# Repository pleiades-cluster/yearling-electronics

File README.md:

# yearling-electronics
PROVES-Yearling Project files for CD&amp;H and EPS boards

C&DH Board Design Requirements: 
The Command and Data Handling (C&DH) Board is the link between our satellite and the rest of the world. The C&DH board will also handle the broad level scheduling of satellite activities. 

Key Requirements: 

- Facilitate Radio Receive and Transmit 
- Collect Satellite State of Health Data 
- Process Satellite Data into Packets for Transmission 
- Schedule High Level Satellite Activities 

Would be nice: 
- Facilitate a live engineering data link with other processors onboard the satellite 
- EPS Board Design Requirements: 

Non-Optional:
- Overcharge Protection
- Overdischarge Protection
- Solar Charging Circuit 
- 3.3V Regulator
- 5V Regulator 
- Inhibit Scheme 
- Battery Monitor

Very Preferred:
- Direct RP2040 Control On-Board 
- Battery Fuel Gauge 
- Power Path Circuit
- Battery Thermal Management 

Would be Nice:
- Circuit Breaker System 
- Resettable Fuses 

The EPS board will be a hybrid of the PyCubed and OreSat architectures.

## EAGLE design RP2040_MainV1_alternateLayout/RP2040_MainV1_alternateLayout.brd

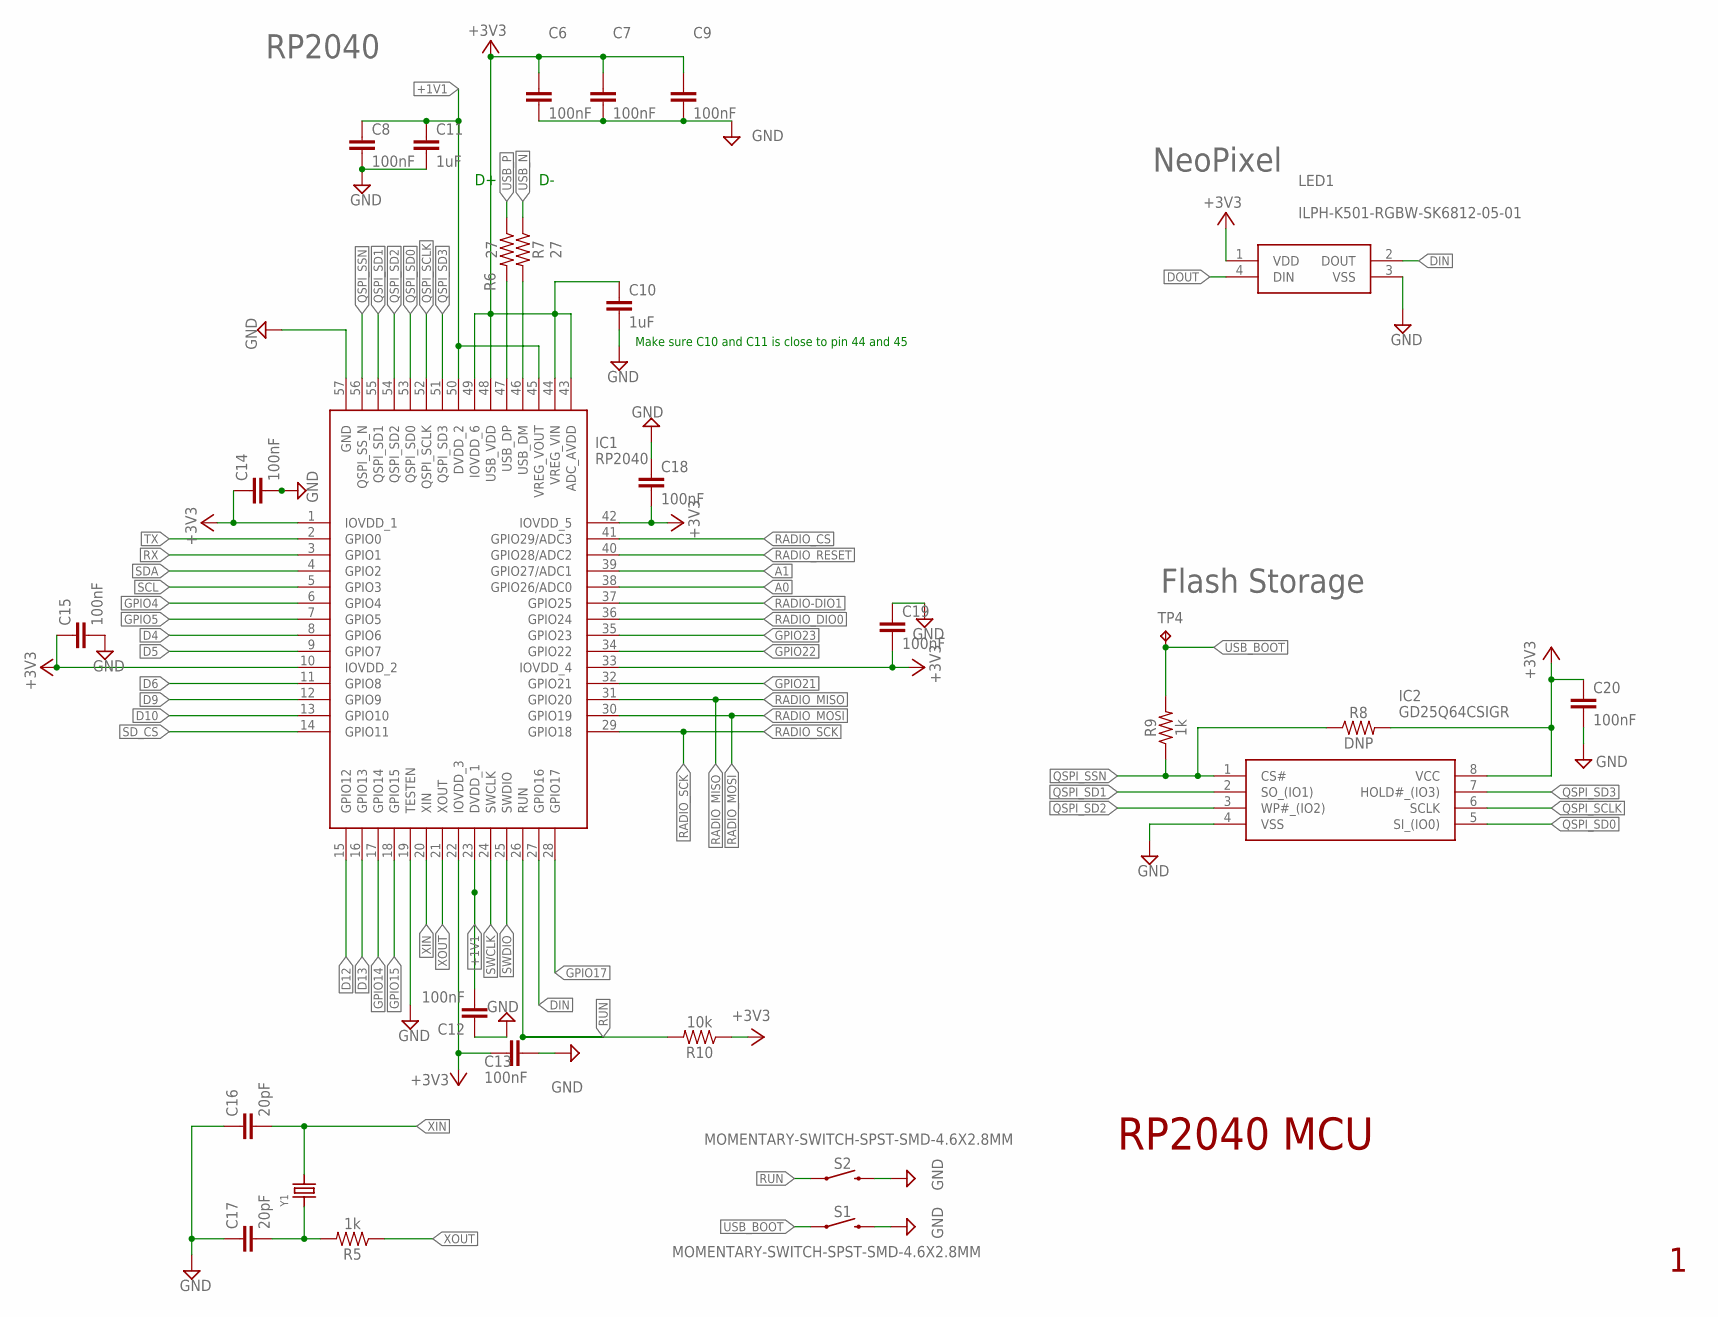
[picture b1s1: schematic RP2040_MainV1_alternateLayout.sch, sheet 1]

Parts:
C6, C7, C8, C9, C12, C13, C14, C15, C18, C19: 100nF; 0402
C10, C11: 1uF; 0402
C16, C17: 20pF; 0603
C20: 100nF; 0603
IC1: RP2040; QFN40P700X700X90-57N
IC2: GD25Q64CSIGR; SOIC127P790X216-8N
LED1: ILPH-K501-RGBW-SK6812-05-01; ILPHK501RGBWSK68120501
R5, R9: 1k; 0603
R6, R7: 27; 0603
R8: DNP; 0603
R10: 10k; 0603
S1, S2: MOMENTARY-SWITCH-SPST-SMD-4.6X2.8MM; TACTILE_SWITCH_SMD_4.6X2.8MM
TP4: TPTP12R; TP12R
Y1: CRYSTAL2.5X2.0MM; CRYSTAL_2.5X2

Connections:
+1V1: C8.1, C11.1, C12.2, IC1.23 (DVDD_1), IC1.45 (VREG_VOUT), IC1.50 (DVDD_2)
+3V3: C6.1, C7.1, C9.1, C10.1, C13.2, C14.1, C15.1, C18.2, C19.2, C20.1, IC1.1 (IOVDD_1), IC1.10 (IOVDD_2), IC1.22 (IOVDD_3), IC1.33 (IOVDD_4), IC1.42 (IOVDD_5), IC1.43 (ADC_AVDD), IC1.44 (VREG_VIN), IC1.48 (USB_VDD), IC1.49 (IOVDD_6), IC2.8 (VCC), LED1.1 (VDD), R8.2, R10.1; also elsewhere on the board
A0: IC1.38 (GPIO26/ADC0); also elsewhere on the board
A1: IC1.39 (GPIO27/ADC1); also elsewhere on the board
D4: IC1.8 (GPIO6); also elsewhere on the board
D5: IC1.9 (GPIO7); also elsewhere on the board
D6: IC1.11 (GPIO8); also elsewhere on the board
D9: IC1.12 (GPIO9); also elsewhere on the board
D10: IC1.13 (GPIO10); also elsewhere on the board
D12: IC1.15 (GPIO12)
D13: IC1.16 (GPIO13)
DIN: IC1.27 (GPIO16), LED1.2 (DOUT)
DOUT: LED1.4 (DIN)
GND: C6.2, C7.2, C8.2, C9.2, C10.2, C11.2, C12.1, C13.1, C14.2, C15.2, C16.1, C17.1, C18.1, C19.1, C20.2, IC1.19 (TESTEN), IC1.57 (GND), IC2.4 (VSS), LED1.3 (VSS), S1.3 (2), S1.4 (2), S2.3 (2), S2.4 (2); also elsewhere on the board
GPIO4: IC1.6 (GPIO4)
GPIO5: IC1.7 (GPIO5)
GPIO14: IC1.17 (GPIO14)
GPIO15: IC1.18 (GPIO15)
GPIO17: IC1.28 (GPIO17)
GPIO21: IC1.32 (GPIO21)
GPIO22: IC1.34 (GPIO22)
GPIO23: IC1.35 (GPIO23)
unnamed: C17.2, R5.2, Y1.1
QSPI_SCLK: IC1.52 (QSPI_SCLK), IC2.6 (SCLK)
QSPI_SD0: IC1.53 (QSPI_SD0), IC2.5 (SI_(IO0))
QSPI_SD1: IC1.55 (QSPI_SD1), IC2.2 (SO_(IO1))
QSPI_SD2: IC1.54 (QSPI_SD2), IC2.3 (WP#_(IO2))
QSPI_SD3: IC1.51 (QSPI_SD3), IC2.7 (HOLD#_(IO3))
QSPI_SSN: IC1.56 (QSPI_SS_N), IC2.1 (CS#), R8.1, R9.1
RADIO-DIO1: IC1.37 (GPIO25); also elsewhere on the board
RADIO_CS: IC1.41 (GPIO29/ADC3); also elsewhere on the board
RADIO_DIO0: IC1.36 (GPIO24); also elsewhere on the board
RADIO_MISO: IC1.31 (GPIO20); also elsewhere on the board
RADIO_MOSI: IC1.30 (GPIO19); also elsewhere on the board
RADIO_RESET: IC1.40 (GPIO28/ADC2); also elsewhere on the board
RADIO_SCK: IC1.29 (GPIO18); also elsewhere on the board
RUN: IC1.26 (RUN), R10.2, S2.1, S2.2 (1)
RX: IC1.3 (GPIO1); also elsewhere on the board
SCL: IC1.5 (GPIO3); also elsewhere on the board
SDA: IC1.4 (GPIO2); also elsewhere on the board
SD_CS: IC1.14 (GPIO11); also elsewhere on the board
SWCLK: IC1.24 (SWCLK); also elsewhere on the board
SWDIO: IC1.25 (SWDIO); also elsewhere on the board
TX: IC1.2 (GPIO0); also elsewhere on the board
USB_BOOT: R9.2, S1.1, S1.2 (1), TP4.TP
USB_DM\: IC1.46 (USB_DM), R7.2
USB_DP: IC1.47 (USB_DP), R6.2
USB_N: R7.1; also elsewhere on the board
USB_P: R6.1; also elsewhere on the board
XIN: C16.2, IC1.20 (XIN), Y1.3 (2)
XOUT: IC1.21 (XOUT), R5.1

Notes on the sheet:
Make sure C10 and C11 is close to pin 44 and 45
RP2040 MCU
RP2040
Flash Storage
NeoPixel

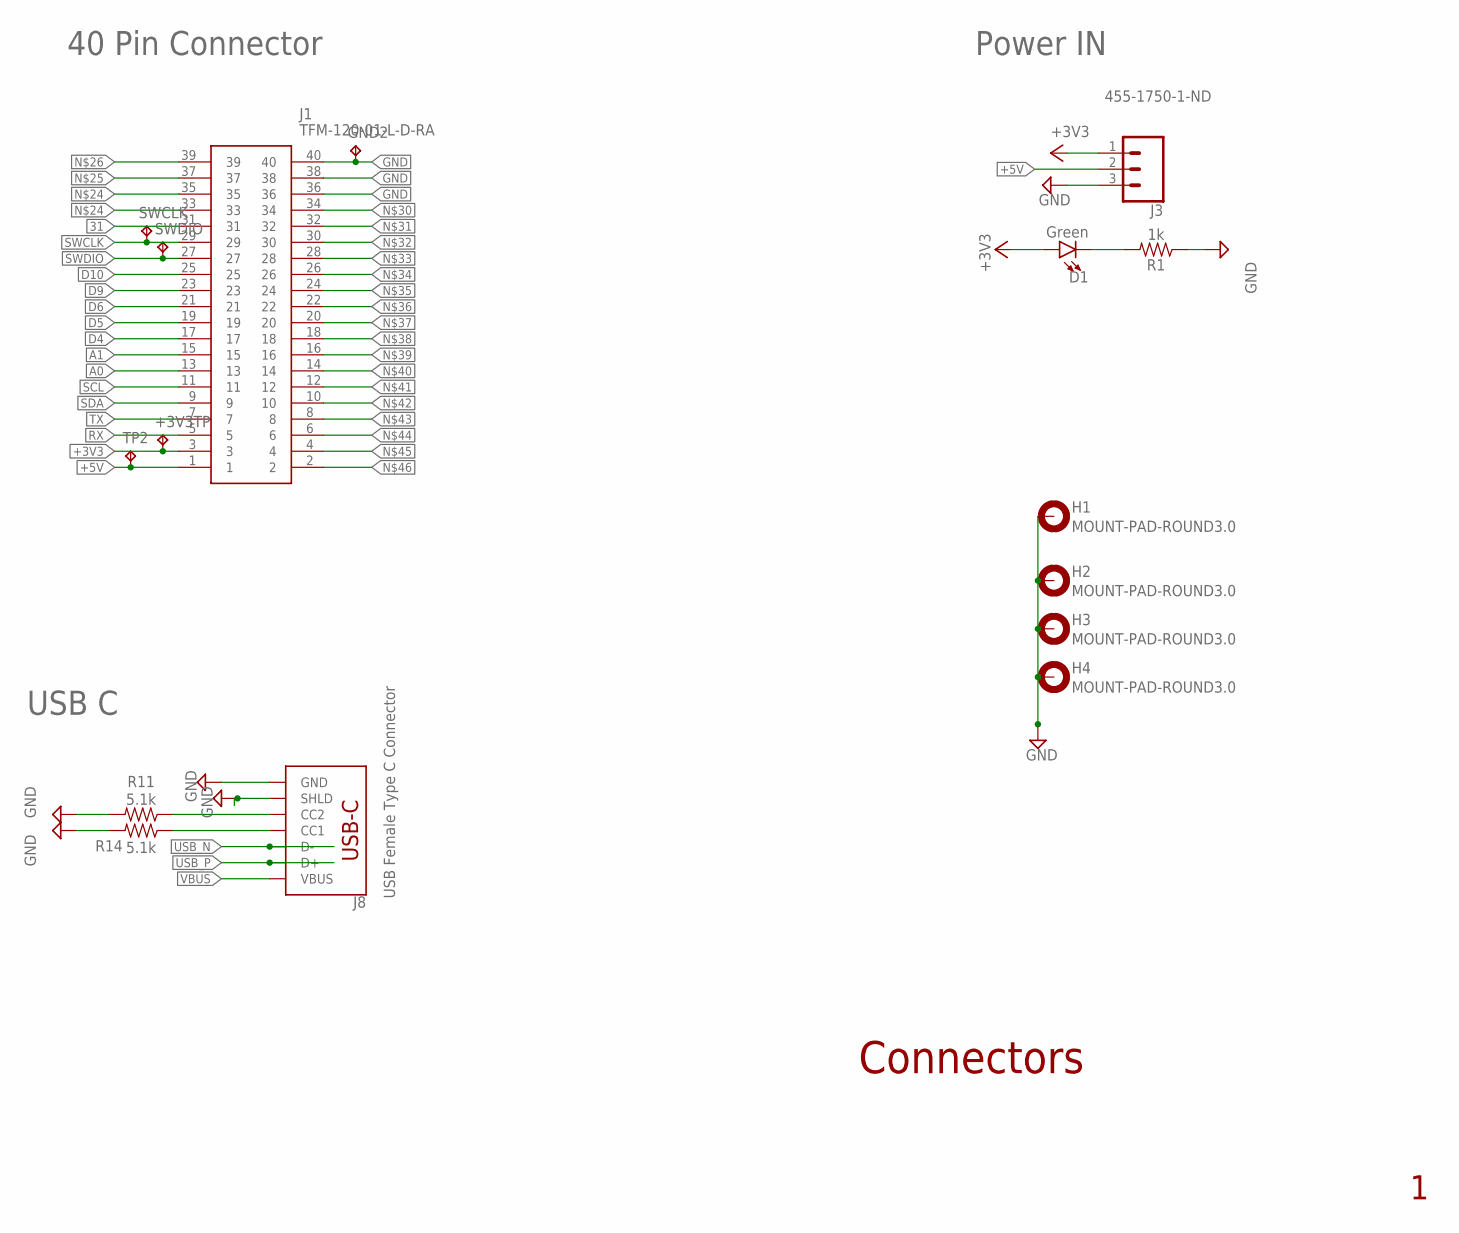
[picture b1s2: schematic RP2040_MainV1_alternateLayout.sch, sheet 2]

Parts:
+3V3TP: TPTP12R; TP12R
D1: Green; LED-0603
GND2: TPTP12R; TP12R
H1, H2, H3, H4: MOUNT-PAD-ROUND3.0; 3,0-PAD
J1: TFM-120-01-L-D-RA; TFM-120-01-XXX-D-RA
J3: 455-1750-1-ND; 1X03
J8: USB Female Type C Connector; USB-C-16P-4LAYER-ISOLATED
R1: 1k; 0603
R11, R14: 5.1k; 0603
SWCLK: TPTP12R; TP12R
SWDIO: TPTP12R; TP12R
TP2: TPTP12R; TP12R

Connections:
31: J1.31
+3V3: +3V3TP.TP, D1.A, J1.3, J3.1; also elsewhere on the board
+5V: J1.1, J3.2, TP2.TP; also elsewhere on the board
A0: J1.13; also elsewhere on the board
A1: J1.15; also elsewhere on the board
D4: J1.17; also elsewhere on the board
D5: J1.19; also elsewhere on the board
D6: J1.21; also elsewhere on the board
D9: J1.23; also elsewhere on the board
D10: J1.25; also elsewhere on the board
GND: GND2.TP, H1.B3,0, H2.B3,0, H3.B3,0, H4.B3,0, J1.36, J1.38, J1.40, J3.3, J8.GND, J8.GND2 (GND), J8.SHLD1 (SHLD), J8.SHLD2 (SHLD), J8.SHLD3 (SHLD), J8.SHLD4 (SHLD), J8.SHLD5 (SHLD), J8.SHLD6 (SHLD), J8.SHLD7 (SHLD), J8.SHLD8 (SHLD), R1.1, R11.2, R14.2; also elsewhere on the board
unnamed: J8.B5 (CC2), R11.1
unnamed: J8.A5 (CC1), R14.1
unnamed: D1.C, R1.2
RX: J1.5; also elsewhere on the board
SCL: J1.11; also elsewhere on the board
SDA: J1.9; also elsewhere on the board
SWCLK: J1.29, SWCLK.TP; also elsewhere on the board
SWDIO: J1.27, SWDIO.TP; also elsewhere on the board
TX: J1.7; also elsewhere on the board
USB_N: J8.A7 (D-), J8.B7 (D-); also elsewhere on the board
USB_P: J8.A6 (D+), J8.B6 (D+); also elsewhere on the board
VBUS: J8.VBUS1 (VBUS), J8.VBUS2 (VBUS)

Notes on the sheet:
Connectors
40 Pin Connector
Power IN
USB C

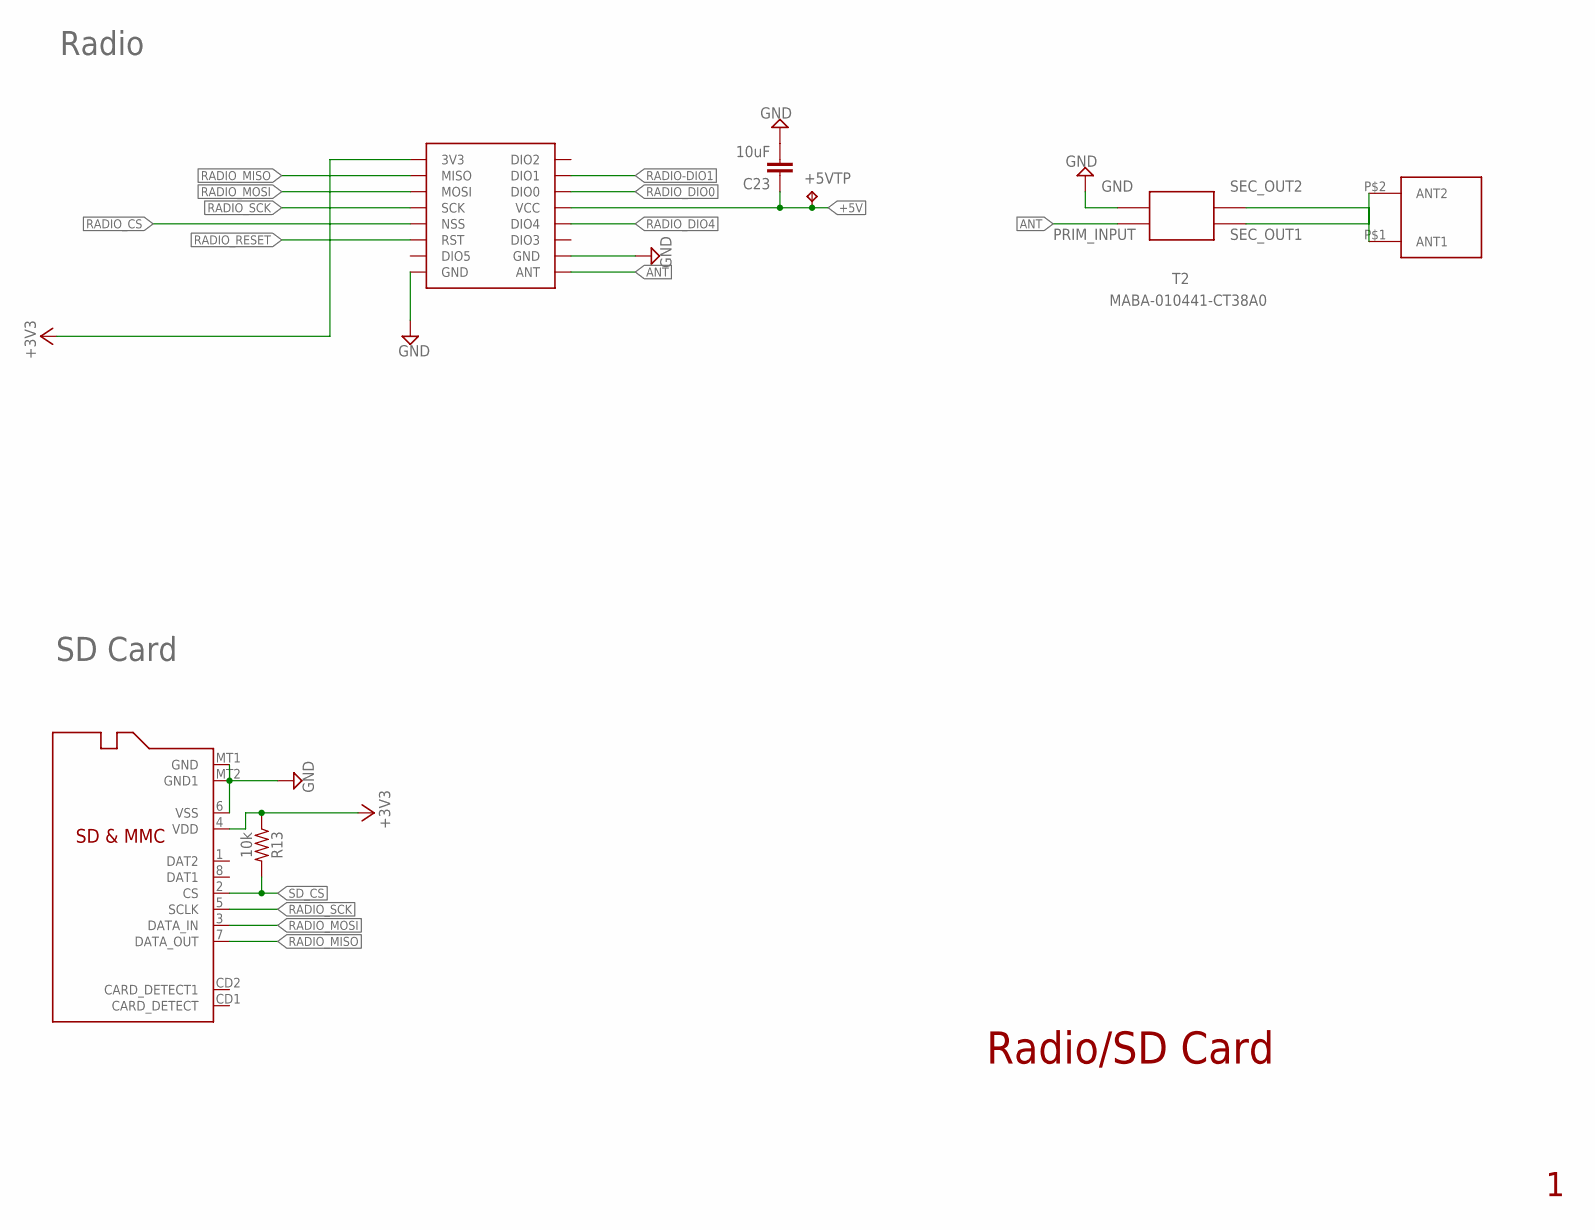
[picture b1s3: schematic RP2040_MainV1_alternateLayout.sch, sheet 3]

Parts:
+5VTP: TPTP12R; TP12R
C23: 10uF; 0603
R13: 10k; 0603
T2: MABA-010441-CT38A0; MABA010441CT38A0
U$1: MICROSD
U$2: RFM95W; RFM95PW
U$4: BIGPAD; BIGPADS

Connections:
+3V3: R13.1, U$1.4 (VDD), U$2.3V3; also elsewhere on the board
+5V: +5VTP.TP, C23.1, U$2.VCC; also elsewhere on the board
ANT: T2.1 (PRIMARY_DOT_(INPUT)), U$2.ANT
GND: C23.2, T2.4 (PRIMARY_(GROUND)), U$1.6 (VSS), U$1.MT1 (GND), U$1.MT2 (GND1), U$2.GND@0 (GND), U$2.GND@1 (GND); also elsewhere on the board
unnamed: T2.2 (SECONDARY_DOT_(OUTPUT_1)), U$4.P$2 (ANT2)
unnamed: T2.3 (SECONDARY_(OUTPUT_2)), U$4.P$1 (ANT1)
RADIO-DIO1: U$2.DIO1; also elsewhere on the board
RADIO_CS: U$2.NSS; also elsewhere on the board
RADIO_DIO0: U$2.DIO0; also elsewhere on the board
RADIO_DIO4: U$2.DIO4
RADIO_MISO: U$1.7 (DATA_OUT), U$2.MISO; also elsewhere on the board
RADIO_MOSI: U$1.3 (DATA_IN), U$2.MOSI; also elsewhere on the board
RADIO_RESET: U$2.RST; also elsewhere on the board
RADIO_SCK: U$1.5 (SCLK), U$2.SCK; also elsewhere on the board
SD_CS: R13.2, U$1.2 (CS); also elsewhere on the board

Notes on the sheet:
Radio/SD Card
Radio
SD Card

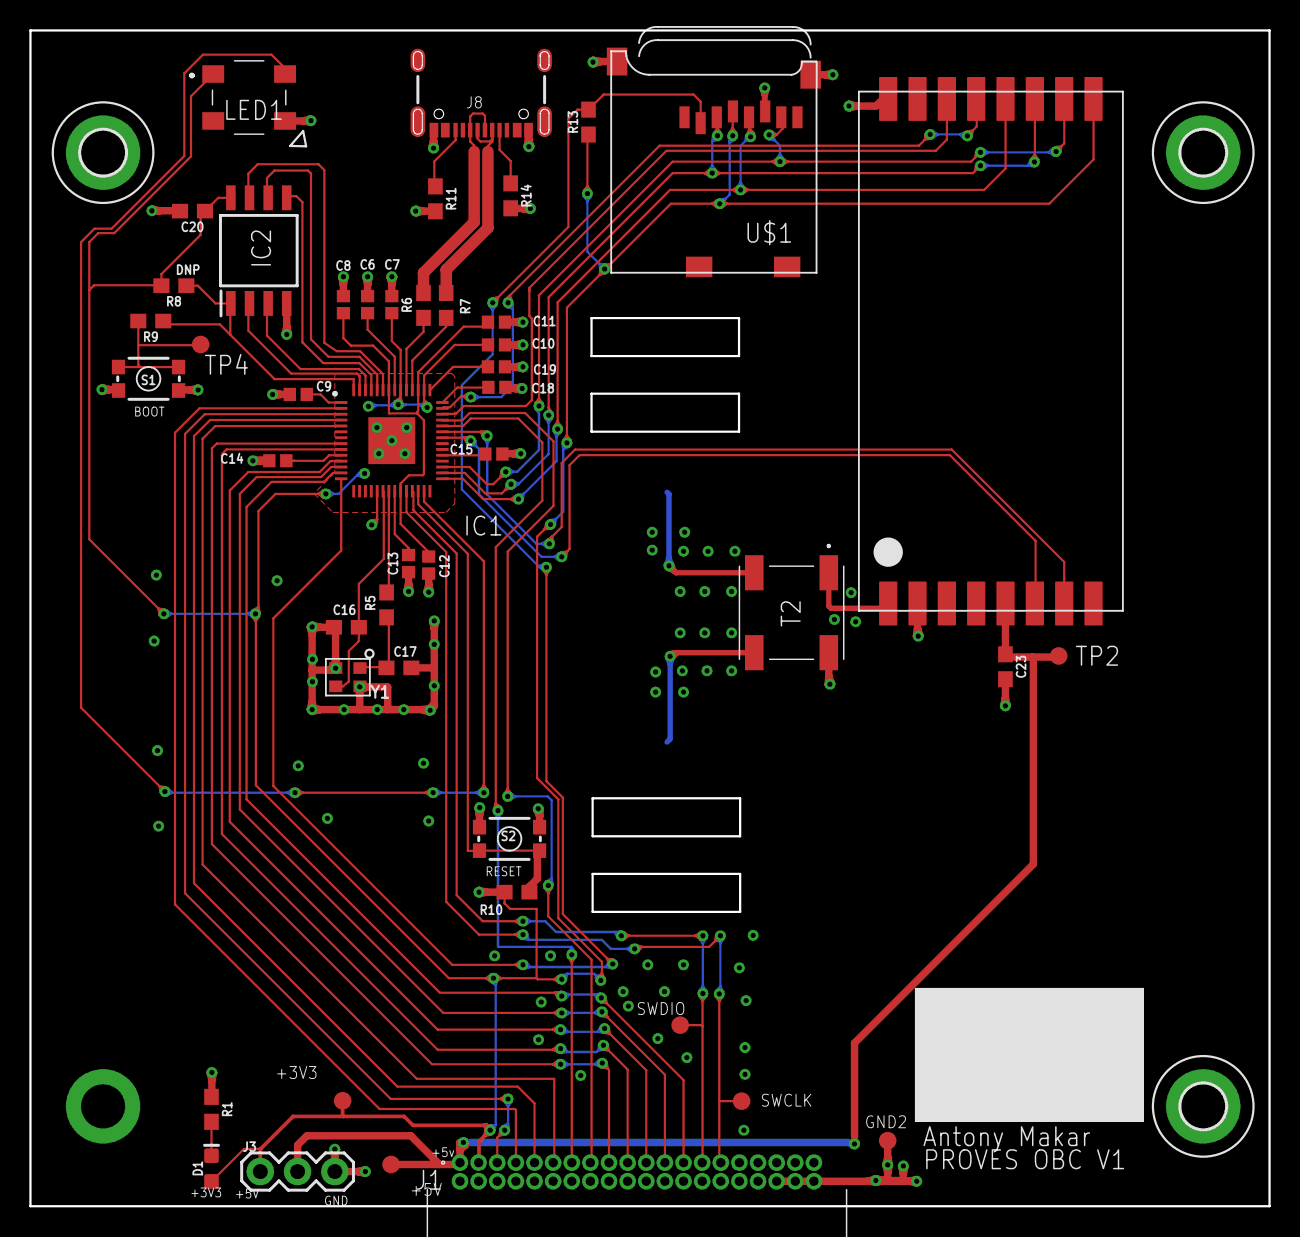
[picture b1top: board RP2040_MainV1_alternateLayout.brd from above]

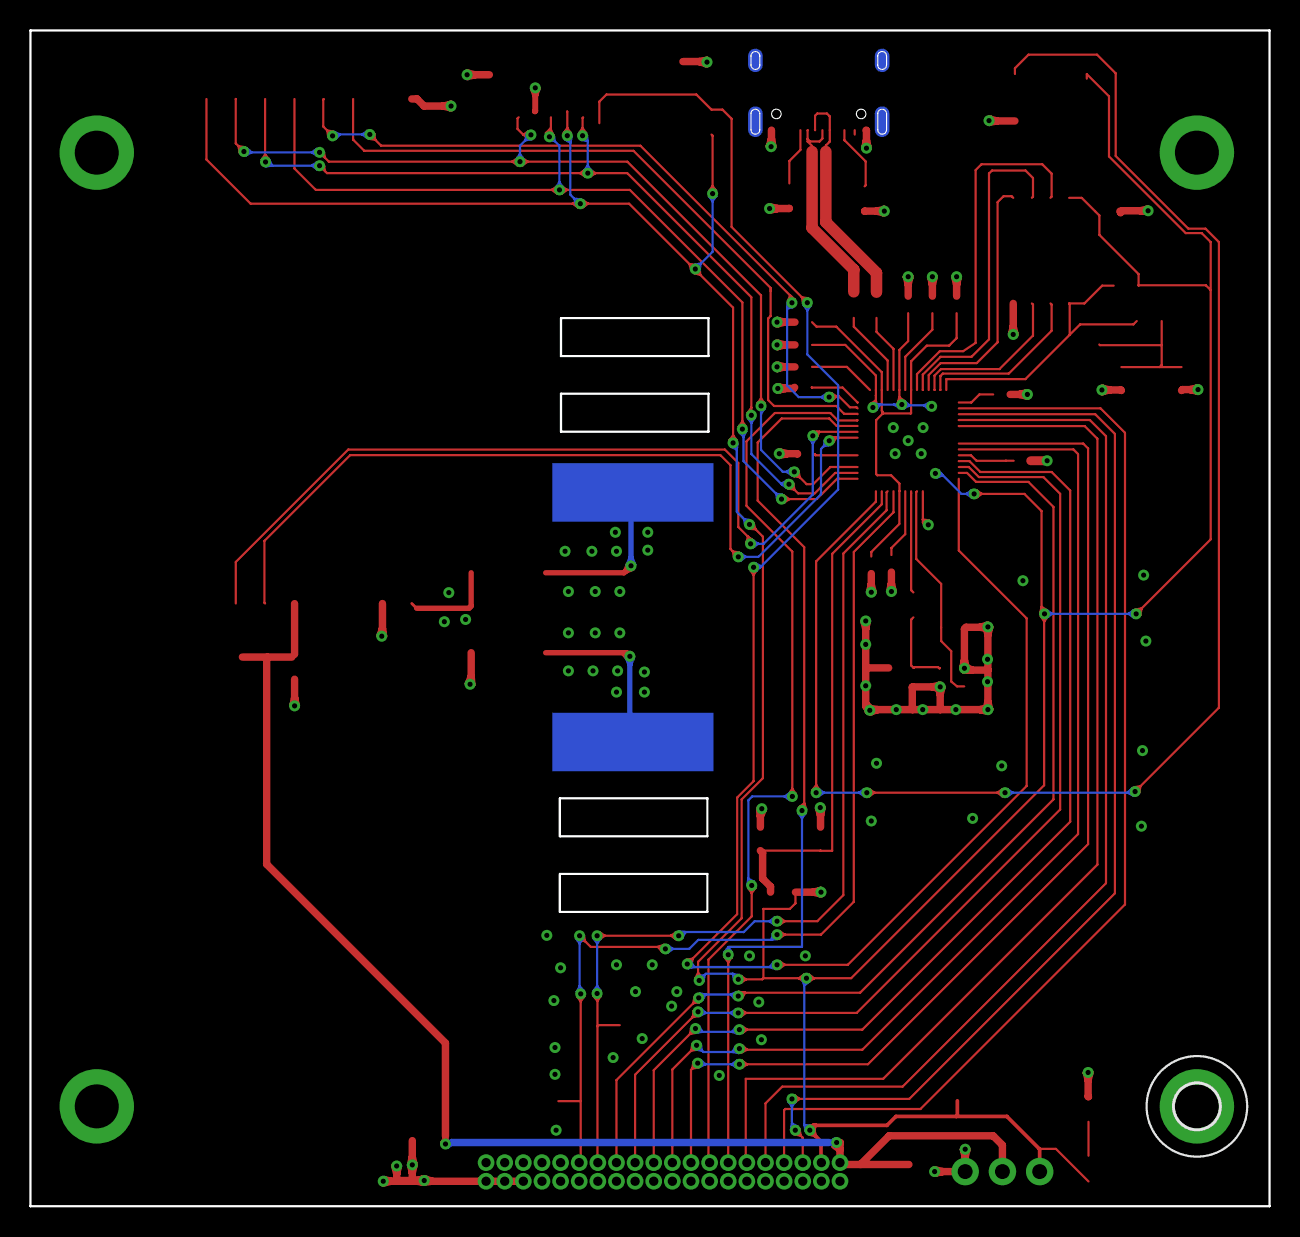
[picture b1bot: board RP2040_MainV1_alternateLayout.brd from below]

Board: 2 copper layers, 84.5 x 80.2 mm, 51 parts (2 on the bottom side), 48 nets.

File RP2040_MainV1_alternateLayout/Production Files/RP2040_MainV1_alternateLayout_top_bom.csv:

Comment,Designator,Footprint,LCSC Part #
,Y1,CRYSTAL_2.5X2,
1k,R1 R5 R9,603,
1uF,C10 C11,402,
5.1k,R11 R14,603,
10k,R10 R13,603,
10uF,C23,603,
20pF,C16 C17,603,
27,R6 R7,603,
100nF,C6 C7 C8 C9 C12 C13 C14 C15 C18 C19 C20,603,
455-1750-1-ND,J3,1X03,
DNP,R8,603,
GD25Q64CSIGR,IC2,SOIC127P790X216-8N,
Green,D1,LED-0603,
ILPH-K501-RGBW-SK6812-05-01,LED1,ILPHK501RGBWSK68120501,
MABA-010441-CT38A0,T2,MABA010441CT38A0,
MICROSD,U$1,MICROSD,
MOMENTARY-SWITCH-SPST-SMD-4.6X2.8MM,S1 S2,TACTILE_SWITCH_SMD_4.6X2.8MM,
MOUNT-PAD-ROUND3.0,H2 H3 H4,3 0-PAD,
RFM95W,U$2,RFM95PW,
RP2040,IC1,QFN40P700X700X90-57N,
TFM-120-01-L-D-RA,J1,TFM-120-01-XXX-D-RA,
TPTP12R,+3V3TP +5VTP GND2 SWCLK SWDIO TP2 TP4,TP12R,
USB Female Type C Connector,J8,USB-C-16P-4LAYER-ISOLATED,

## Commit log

2022-04-05 Added 18650 Batteries and protection circuit
2022-04-11 Initial Commit
    All of the Eagle Files from Antony's V1a OneDrive Folder
2022-04-15 Add files via upload
    im so sorry for the million V0 backup files XD this has the 'V1" schem with new solar and ADC ckt
2022-04-15 EPS V1.5
    Major file cleanup, combined V1 files from Christeen and Austin, added gitignore to remove backup and extra files.
2022-04-15 Quick Cleanup
    Added ToDo's, not much else need sleep
2022-04-15 Added 5V Reg and Heater
2022-04-15 Edited ToDo's
    99% of features are now implemented, need to clean up nets and add footprints for MPPT IC's.
    Then ready for layout!
2023-02-01 Saddle Board
2023-02-01 Final As Ordered Feb 1, 2023

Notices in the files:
parts and their libraries:
SparkFun-Resistors: Licensing: Creative Commons ShareAlike 4.0 International - https://creativecommons.org/licenses/by-sa/4.0
microbuilder: This work is placed in the public domain, and may be freely used for commercial and non-commercial work with the following conditions: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
